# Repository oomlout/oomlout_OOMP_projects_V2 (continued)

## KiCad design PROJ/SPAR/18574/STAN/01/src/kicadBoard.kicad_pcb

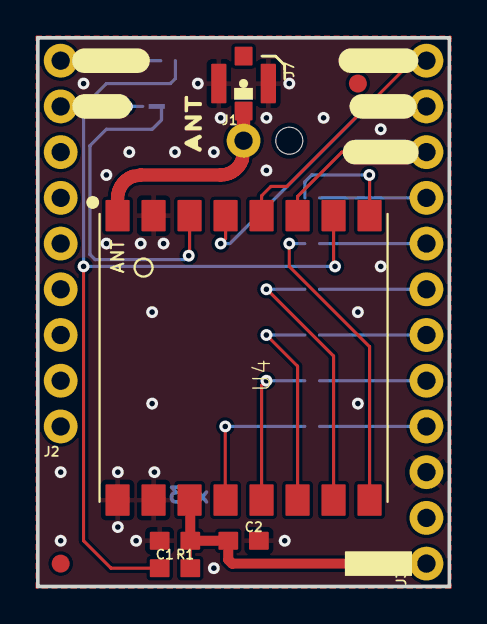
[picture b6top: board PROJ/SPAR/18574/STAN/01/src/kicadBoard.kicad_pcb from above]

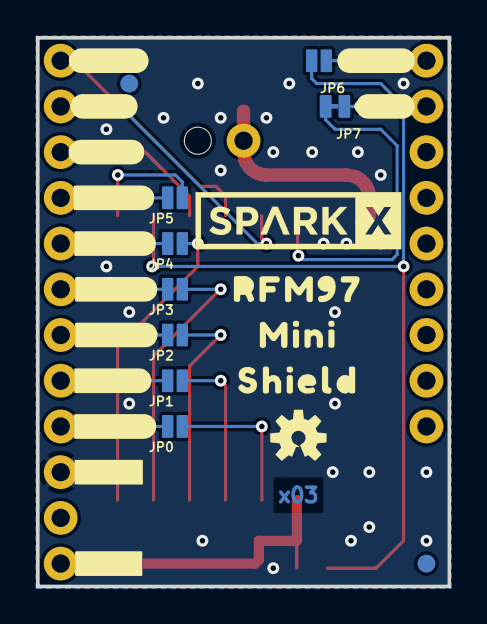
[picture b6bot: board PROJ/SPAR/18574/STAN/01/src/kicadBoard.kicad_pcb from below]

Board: 2 copper layers, 22.9 x 30.5 mm, 47 parts (28 on the bottom side), 22 nets.

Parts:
@HOLE0: (no value)
C1: 10uF; 0603
C2: 0.1uF; 0603
FID1, FID2, FID3, FID4: FIDUCIAL1X2; FIDUCIAL-1X2
FRAME1: FRAME-LETTER; CREATIVE_COMMONS
J1: 1X01_NO_SILK
J2: 1X09_NO_SILK
J3: 1X12_NO_SILK
J7: U.FL
JP0, JP1, JP2, JP3, JP4, JP5, JP6: JUMPER-SMT_2_NO_NO-SILK; SMT-JUMPER_2_NO_NO-SILK
JP7: JUMPER-SMT_2_NC_TRACE_NO-SILK; SMT-JUMPER_2_NC_TRACE_NO-SILK
LOGO2: OSHW-LOGOS; OSHW-LOGO-S
R1: 10k; 0603
U4: RFM97CW; RFM97
U$1: ANT0
U$2, U$21: ##CS##2
U$3, U$7: #SDO#0
U$4, U$6: #SDI#1
U$5, U$12: #SCK#0
U$8, U$9: #3V3#0
U$10: #GND#1
U$11: MINI0
U$13, U$17: ##RST##0
U$19: RFM970
U$20: SHIELD2
U$22: SPARKX-LOGO5; SPARKX-LARGE
U$23: #DIO0#0
U$24: #DIO1#0
U$25: #DIO2#0
U$26: #DIO3#0
U$27: #DIO4#0
U$28: #DIO5#0

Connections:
3.3V: C1.1, C2.1, J3.1, R1.2, U4.3V3
ANT: J1.1, J7.FEED, U4.ANT
DIO0: JP0.1, U4.DIO0
DIO1: JP1.1, U4.DIO1
DIO2: JP2.1, U4.DIO2
DIO3: JP3.1, U4.DIO3
DIO4: JP4.1, U4.DIO4
DIO5: JP5.1, U4.DIO5
GND: C1.2, C2.2, J3.3, J7.1, J7.2, U4.GND, U4.GND@1, U4.GND@2
unnamed: J3.6, JP2.2
unnamed: J2.9, JP6.2
unnamed: J2.8, JP7.2
unnamed: J3.5, JP1.2
unnamed: J3.4, JP0.2
unnamed: J3.7, JP3.2
unnamed: J3.8, JP4.2
unnamed: J3.9, JP5.2
SCK: J3.10, U4.SCK
SDI: J3.11, U4.SDI
SDO: J3.12, U4.SDO
~CS: JP7.1, U4.!CS!
~RST: JP6.1, R1.1, U4.!RST

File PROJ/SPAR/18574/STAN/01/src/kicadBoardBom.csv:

"Id";"Designator";"Package";"Quantity";"Designation";"Supplier and ref";
1;"U$1";"ANT0";1;"";;;
2;"U$5,U$12";"#SCK#0";2;"";;;
3;"C1";"0603";1;"10uF";;;
4;"U4";"RFM97";1;"RFM97CW";;;
5;"U$4,U$6";"#SDI#1";2;"";;;
6;"J3";"1X12_NO_SILK";1;"";;;
7;"@HOLE0";"";1;"";;;
8;"U$8,U$9";"#3V3#0";2;"";;;
9;"FID2,FID1,FID4,FID3";"FIDUCIAL-1X2";4;"FIDUCIAL1X2";;;
10;"C2";"0603";1;"0.1uF";;;
11;"U$3,U$7";"#SDO#0";2;"";;;
12;"R1";"0603";1;"10k";;;
13;"U$21,U$2";"##CS##2";2;"";;;
14;"J1";"1X01_NO_SILK";1;"";;;
15;"FRAME1";"CREATIVE_COMMONS";1;"FRAME-LETTER";;;
16;"U$13,U$17";"##RST##0";2;"";;;
17;"J7";"U.FL";1;"U.FL";;;
18;"J2";"1X09_NO_SILK";1;"";;;
19;"JP6,JP2,JP4,JP1,JP0,JP3,JP5";"SMT-JUMPER_2_NO_NO-SILK";7;"JUMPER-SMT_2_NO_NO-SILK";;;
20;"U$23";"#DIO0#0";1;"";;;
21;"U$28";"#DIO5#0";1;"";;;
22;"U$19";"RFM970";1;"";;;
23;"U$10";"#GND#1";1;"";;;
24;"U$11";"MINI0";1;"";;;
25;"JP7";"SMT-JUMPER_2_NC_TRACE_NO-SILK";1;"JUMPER-SMT_2_NC_TRACE_NO-SILK";;;
26;"U$22";"SPARKX-LARGE";1;"SPARKX-LOGO5";;;
27;"U$26";"#DIO3#0";1;"";;;
28;"LOGO2";"OSHW-LOGO-S";1;"OSHW-LOGOS";;;
29;"U$24";"#DIO1#0";1;"";;;
30;"U$25";"#DIO2#0";1;"";;;
31;"U$27";"#DIO4#0";1;"";;;
32;"U$20";"SHIELD2";1;"";;;

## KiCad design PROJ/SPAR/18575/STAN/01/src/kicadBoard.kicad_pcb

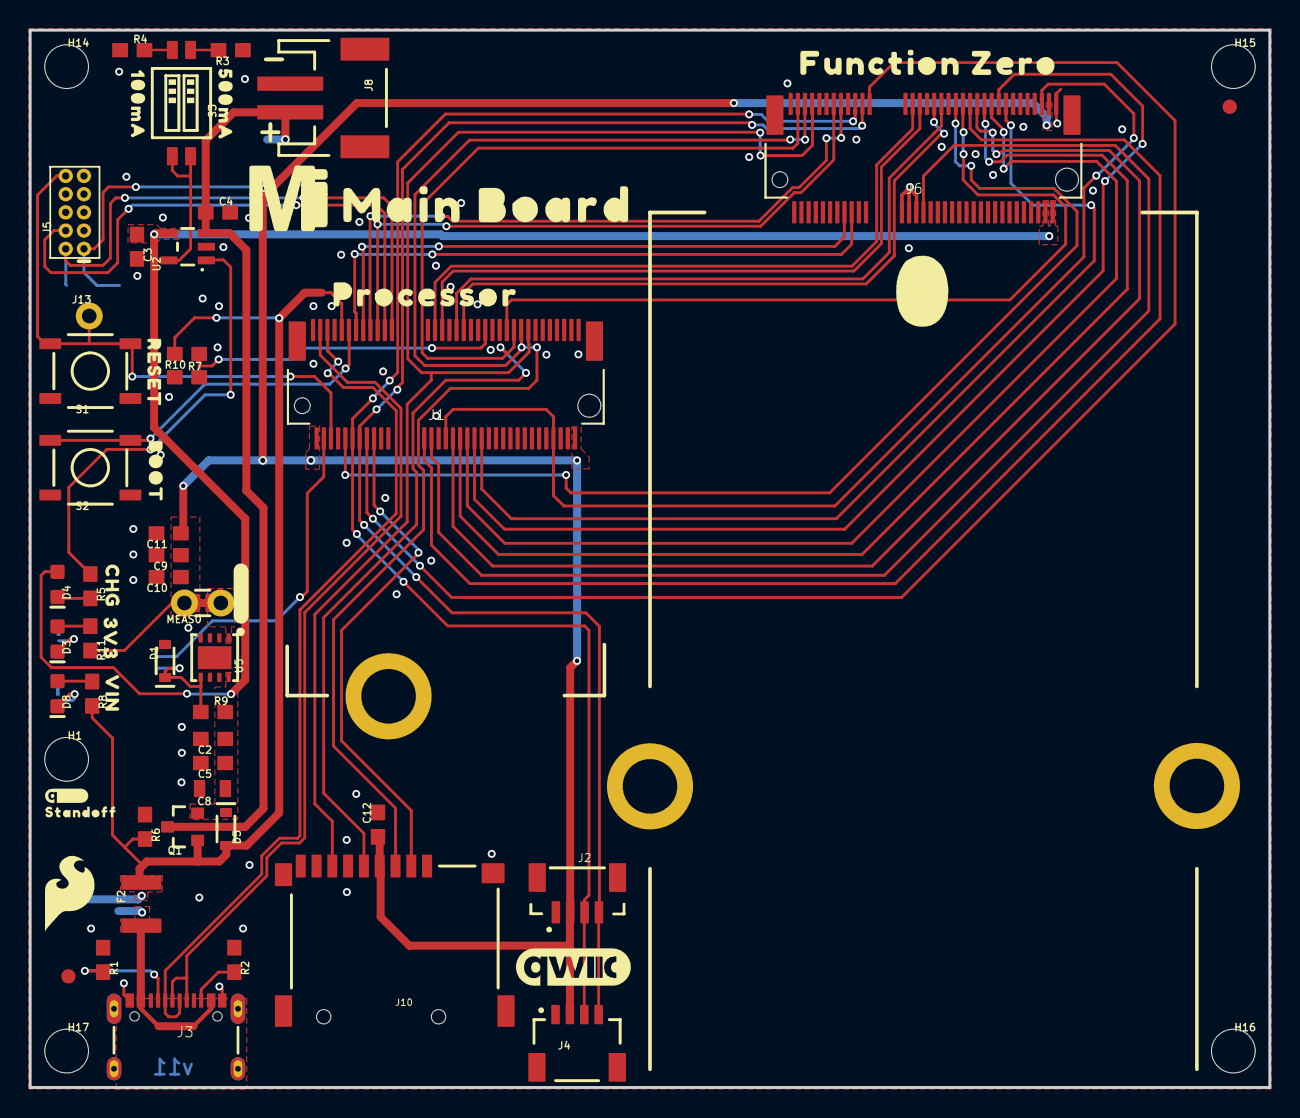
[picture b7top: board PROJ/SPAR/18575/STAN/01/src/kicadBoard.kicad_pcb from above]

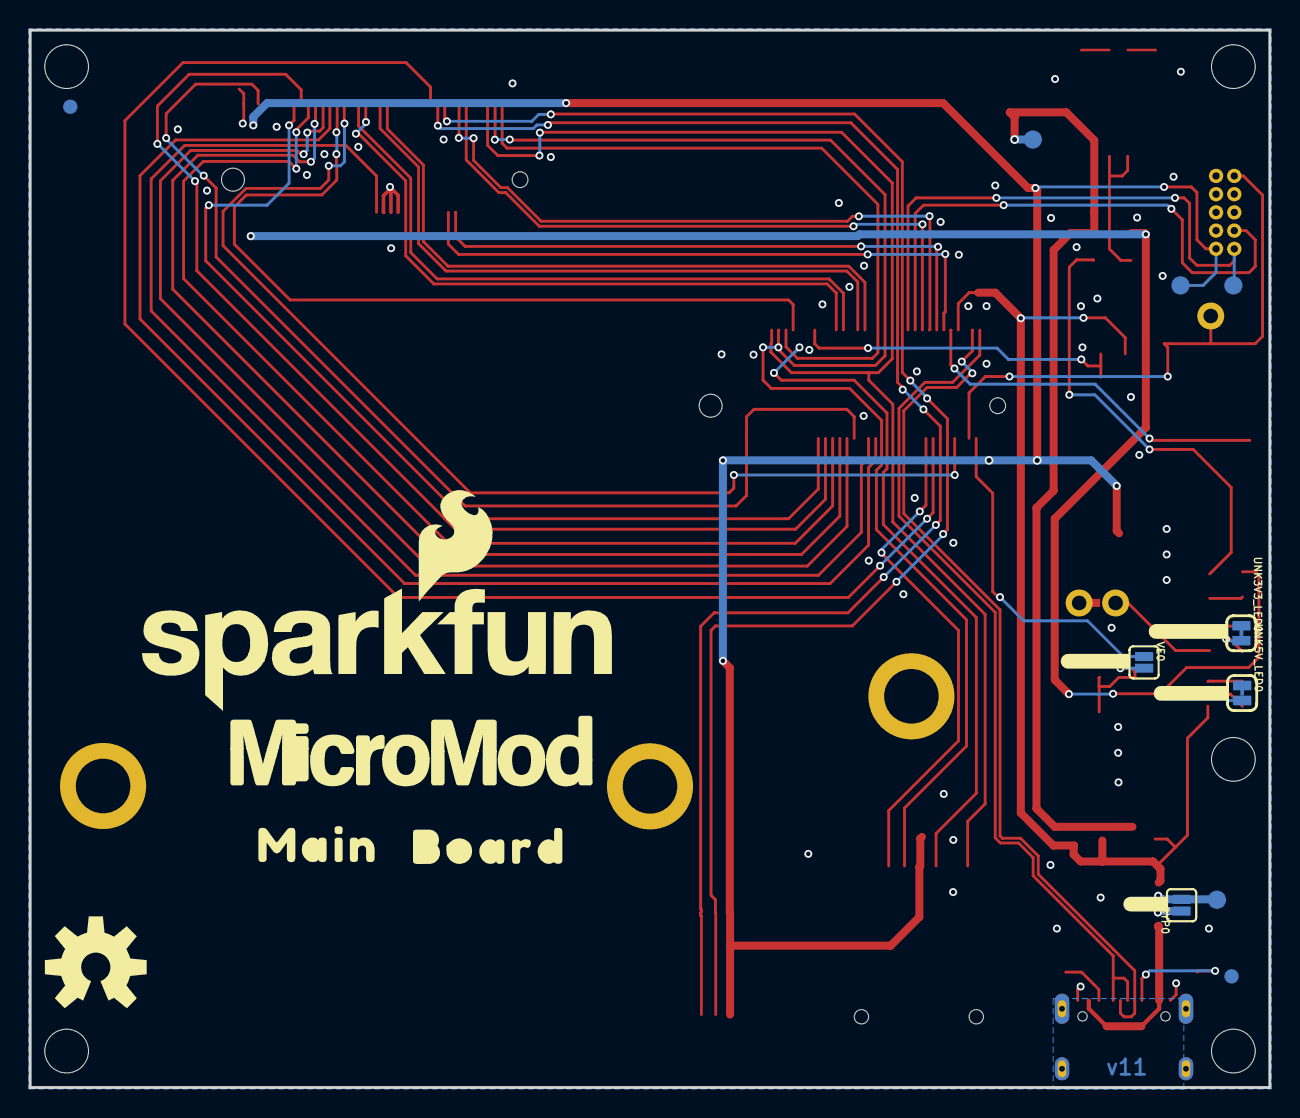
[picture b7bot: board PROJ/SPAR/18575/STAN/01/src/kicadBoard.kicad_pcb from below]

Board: 2 copper layers, 86.4 x 73.7 mm, 89 parts (19 on the bottom side), 52 nets.

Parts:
BYP0: JUMPER-SMT_2_NO_SILK; SMT-JUMPER_2_NO_SILK
C2, C11: 0.22uF; 0603
C3, C4: 4.7uF; 0603
C5, C10, C12: 0.1uF; 0603
C8: 10uF; 0805
C9: 1.0uF; 0603
D1: 3.3V; SOD-323
D3, D8: RED; LED-0603
D4: Yellow; LED-0603
D5: 1A/23V/620mV; SOD-323
F2: 6V/2A; 1210
FD1, FD2, FD3, FD4: FIDUCIAL1X2; FIDUCIAL-1X2
FRAME1: FRAME-LEDGER; CREATIVE_COMMONS
H1, H14, H15, H16, H17: STAND-OFFTIGHT; STAND-OFF-TIGHT
H3, H4, H8: STAND-OFF-REFLOW-M2.5_2.5MM_TALL; STAND-OFF-REFLOW-M2.5
J1: MICROMOD-2222-C; M.2-CONNECTOR-E
J2: Vertical Qwiic Connector; JST04_1MM_VERT
J3: USB-C-16P-2LAYER-PADS
J4: QWIIC_RIGHT_ANGLE; JST04_1MM_RA
J5: CORTEX_JTAG_DEBUG_MINIMUM_PTH; 2X5-PTH-1.27MM
J6: MICROMOD_FUNCTION_MAIN; M.2-CONNECTOR-E-FUNCTION-STANDARD
J8: JST-2-SMD
J10: MICRO-SD-PUSH-PUSH-EXT-PIN; MICROSD-EXTERNALPIN
J13: 1X01_NO_SILK
LOGO1: QWIIC_LOGO_8MM; QWIIC_8MM
LOGO2: SFE_LOGO_NAME_FLAME.3_INCH; SFE_LOGO_NAME_FLAME_.3
LOGO3: OSHW-LOGOL; OSHW-LOGO-L
MEAS0: JUMPER-COMBO_2_NC_TRACE; COMBO-JUMPER_2_NC_TRACE
Q1: 3.1A/30V/105mΩ; SOT23-3
R1, R2: 5.1k; 0603
R3: 2.0k; 0603
R4, R6, R7: 10k; 0603
R5, R11: 1k; 0603
R8: 4.7k; 0603
R9: 100k; 0603
R10: 20k; 0603
S1: Reset; TACTILE_SWITCH_SMD_5.2MM
S2: BOOT; TACTILE_SWITCH_SMD_5.2MM
S3: DIP-02-SMD-50MIL; DIPSWITCH-02-50MIL
TP1, TP2, TP3, TP4: TEST-POINT3X5; PAD.03X.05
U2: MCP73831; SOT23-5
U5: AP7361C-33; UDFN-8
U$1: 3V332530
U$2: VIN32529
U$3: CHG32528
U$4: FUNCTION_ZERO517
U$5: PROCESSOR522
U$6: #3V3_LED#17
U$7: #VIN_LED#16
U$8: #PTC#18
U$9: BOOT32541
U$10: RESET32540
U$11: #3V3_EN#18
U$12: MICROMOD_MI_LOGO_1
U$13: 0525
U$14: MICROMOD_LOGO_1
U$15: MAIN523
U$16: BOARD524
U$17: 100MA6
U$18: 500MA101
U$19: MAIN_BOARD5523
U$20: QWIIC_3MM
U$21: STANDOFF501
U$22: SFE_LOGO_FLAME_.2
U$23: #MEAS#40313513
UNK3V3_LED0, UNK5V_LED0: JUMPER-SMT_2_NC_TRACE_SILK; SMT-JUMPER_2_NC_TRACE_SILK
VE0: JUMPER-SMT_2_NO_SILK; SMT-JUMPER_2_NO_SILK

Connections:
3.3V: C9.1, C10.1, C11.1, C12.1, J1.2, J1.74, J2.2, J4.2, J5.1, J6.73, J10.4, MEAS0.2, MEAS0.4, R11.2, TP2.1
3.3V_EN: J1.4, VE0.1
3.3V_EN_VE: D3.A, R11.1
A0-PROCESSOR: J1.34, J6.38
CTS1-PROCESSOR: J1.15, J6.16
D0-PROCESSOR: J1.10, J6.47
D1-PROCESSOR/SD_CARD_~CS: J1.18, J10.2
D+: J1.3, J3.A6, J3.B6
D-: J1.5, J3.A7, J3.B7
G0-PROCESSOR: J1.40, J6.53
G1-PROCESSOR: J1.42, J6.55
G2-PROCESSOR: J1.44, J6.57
G3-PROCESSOR: J1.46, J6.59
G4-PROCESSOR: J1.48, J6.61
GND: C2.2, C3.2, C4.2, C5.2, C8.2, C9.2, C10.2, C11.2, C12.2, D1.A, H3.1, H4.1, H8.1, J1.1, J1.7, J1.33, J1.36, J1.39, J1.45, J1.75, J2.1, J3.GND, J3.GND2, J4.1, J5.3, J5.5, J5.9, J6.1, J6.32, J6.33, J6.34, J6.36, J6.39, J6.45, J6.75, J8.1, J10.6, J10.10, J10.11, J10.12, J10.13, R1.1, R2.1, R3.1, R4.1, R6.1, R7.1, S1.1, S1.2, S2.1, S2.2, U2.2, U5.4, U5.EP, UNK3V3_LED0.1, UNK5V_LED0.1
HOST_D+: J1.35, J6.35
HOST_D-: J1.37, J6.37
I2C_SCL: J1.14, J2.4, J4.4, J6.21
I2C_SDA: J1.12, J2.3, J4.3, J6.19
I2C_~INT: J1.16, J6.23
unnamed: D1.C, R9.1, U5.5, VE0.2
unnamed: BYP0.1, F2.1, J3.VBUS1, J3.VBUS2
unnamed: J3.A5, R1.2
unnamed: MEAS0.1, MEAS0.3, U5.1
unnamed: D8.A, R8.1
unnamed: R4.2, S3.2
unnamed: D4.C, R5.2
unnamed: D3.C, UNK3V3_LED0.2
unnamed: S3.3, S3.4, U2.5
unnamed: D8.C, UNK5V_LED0.2
unnamed: R5.1, U2.1
unnamed: R3.2, S3.1
PROCESSOR_CAN-RX: J1.41, J6.43
PROCESSOR_CAN-TX: J1.43, J6.41
PWM0-PROCESSOR: J1.32, J6.51
PWR_EN0: J1.38, J1.68, J6.71
RTS1-PROCESSOR: J1.13, J6.18
RX1-PROCESSOR: J1.19, J6.13
SHLD: J3.B5, R2.2
SPI_PROCESSOR_SCK: J1.57, J6.3, J10.5
SPI_PROCESSOR_SDI: J1.61, J6.7, J10.7
SPI_PROCESSOR_SDO: J1.59, J6.5, J10.3
SWDCK: J1.21, J5.4
SWDIO: J1.23, J5.2, TP1.1
TX1-PROCESSOR: J1.17, J6.15
VCC: C2.1, C3.1, C5.1, C8.1, D4.A, D5.C, J6.72, J6.74, Q1.2, R9.2, U2.4, U5.8
VIN: BYP0.2, D5.A, F2.2, J1.9, Q1.1, R6.2, R8.2, R10.2, TP4.1
VIN/3: J1.49, R7.2, R10.1
V_BATT: C4.1, J8.2, Q1.3, TP3.1, U2.3
~BOOT: J1.11, S2.3, S2.4
~CS0-PROCESSOR: J1.55, J6.49
~RESET: J1.6, J5.10, J13.1, S1.3, S1.4

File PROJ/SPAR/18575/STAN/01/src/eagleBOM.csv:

"Part";"Value";"Device";"Package";"Description";"DESIGNER";"PROD_ID";"REV";"SF_ID";"VALUE";
"3V3_LED";"JUMPER-SMT_2_NC_TRACE_SILK";"JUMPER-SMT_2_NC_TRACE_SILK";"SMT-JUMPER_2_NC_TRACE_SILK";"Normally closed trace jumper";"";"";"";"";"";
"5V_LED";"JUMPER-SMT_2_NC_TRACE_SILK";"JUMPER-SMT_2_NC_TRACE_SILK";"SMT-JUMPER_2_NC_TRACE_SILK";"Normally closed trace jumper";"";"";"";"";"";
"BYP";"JUMPER-SMT_2_NO_SILK";"JUMPER-SMT_2_NO_SILK";"SMT-JUMPER_2_NO_SILK";"Normally open jumper";"";"";"";"";"";
"C2";"0.22uF";"0.22UF-0603-25V-10%";"0603";"0.22µF ceramic capacitors";"";"CAP-07822";"";"";"0.22uF";
"C3";"4.7uF";"4.7UF-0603-6.3V-(10%)";"0603";"4.7µF ceramic capacitors";"";"CAP-08280";"";"";"4.7uF";
"C4";"4.7uF";"4.7UF-0603-35V-(20%)";"0603";"4.7µF ceramic capacitors";"";"CAP-14106";"";"";"4.7uF";
"C5";"0.1uF";"0.1UF-0603-25V-(+80/-20%)";"0603";"0.1µF ceramic capacitors";"";"CAP-00810";"";"";"0.1uF";
"C8";"10uF";"10UF-0805-10V-10%";"0805";"10.0µF ceramic capacitors";"";"CAP-11330";"";"";"10uF";
"C9";"1.0uF";"1.0UF-0603-16V-10%";"0603";"1µF ceramic capacitors";"";"CAP-00868";"";"";"1.0uF";
"C10";"0.1uF";"0.1UF-0603-25V-(+80/-20%)";"0603";"0.1µF ceramic capacitors";"";"CAP-00810";"";"";"0.1uF";
"C11";"0.22uF";"0.22UF-0603-25V-10%";"0603";"0.22µF ceramic capacitors";"";"CAP-07822";"";"";"0.22uF";
"C12";"0.1uF";"0.1UF-0603-25V-(+80/-20%)";"0603";"0.1µF ceramic capacitors";"";"CAP-00810";"";"";"0.1uF";
"D1";"3.3V";"DIODE-ZENER-MM3Z3V3T1G";"SOD-323";"Zener Diode";"";"DIO-11284";"";"";"3.3V";
"D3";"RED";"LED-RED0603";"LED-0603";"Red SMD LED";"";"DIO-00819";"";"";"RED";
"D4";"Yellow";"LED-YELLOW0603";"LED-0603";"Yellow SMD LED";"";"DIO-09003";"";"";"Yellow";
"D5";"1A/23V/620mV";"DIODE-SCHOTTKY-BAT20J";"SOD-323";"Schottky diode";"";"DIO-11623";"";"";"1A/23V/620mV";
"D8";"RED";"LED-RED0603";"LED-0603";"Red SMD LED";"";"DIO-00819";"";"";"RED";
"F2";"6V/2A";"PPTC_6V2A";"1210";"Resettable Fuse PPTC";"";"RES-14313";"";"";"6V/2A";
"FD1";"FIDUCIAL1X2";"FIDUCIAL1X2";"FIDUCIAL-1X2";"Fiducial Alignment Points";"";"";"";"";"";
"FD2";"FIDUCIAL1X2";"FIDUCIAL1X2";"FIDUCIAL-1X2";"Fiducial Alignment Points";"";"";"";"";"";
"FD3";"FIDUCIAL1X2";"FIDUCIAL1X2";"FIDUCIAL-1X2";"Fiducial Alignment Points";"";"";"";"";"";
"FD4";"FIDUCIAL1X2";"FIDUCIAL1X2";"FIDUCIAL-1X2";"Fiducial Alignment Points";"";"";"";"";"";
"FRAME1";"FRAME-LEDGER";"FRAME-LEDGER";"CREATIVE_COMMONS";"Schematic Frame - Ledger";"";"";"";"";"";
"H3";"STAND-OFF-REFLOW-M2.5_2.5MM_TALL";"STAND-OFF-REFLOW-M2.5_2.5MM_TALL";"STAND-OFF-REFLOW-M2.5";"Stand Off Reflow Compatible";"";"HW-14899";"";"";"";
"H4";"STAND-OFF-REFLOW-M2.5_2.5MM_TALL";"STAND-OFF-REFLOW-M2.5_2.5MM_TALL";"STAND-OFF-REFLOW-M2.5";"Stand Off Reflow Compatible";"";"HW-14899";"";"";"";
"H8";"STAND-OFF-REFLOW-M2.5_2.5MM_TALL";"STAND-OFF-REFLOW-M2.5_2.5MM_TALL";"STAND-OFF-REFLOW-M2.5";"Stand Off Reflow Compatible";"";"HW-14899";"";"";"";
"H14";"STAND-OFFTIGHT";"STAND-OFFTIGHT";"STAND-OFF-TIGHT";"Stand Off";"";"";"";"";"";
"H15";"STAND-OFFTIGHT";"STAND-OFFTIGHT";"STAND-OFF-TIGHT";"Stand Off";"";"";"";"";"";
"H16";"STAND-OFFTIGHT";"STAND-OFFTIGHT";"STAND-OFF-TIGHT";"Stand Off";"";"";"";"";"";
"H17";"STAND-OFFTIGHT";"STAND-OFFTIGHT";"STAND-OFF-TIGHT";"Stand Off";"";"";"";"";"";
"J1";"MICROMOD-2222-C";"MICROMOD-2222-C";"M.2-CONNECTOR-E";"MicroMod Connector";"";"CONN-14877";"";"";"";
"J2";"Vertical Qwiic Connector";"QWIIC_CONNECTOR";"JST04_1MM_VERT";"SparkFun I2C Standard Qwiic Connector";"";"CONN-14483";"";"";"Vertical Qwiic Connector";
"J3";"";"USB_C_2-LAYER_PADS";"USB-C-16P-2LAYER-PADS";"USB Type C 16Pin Connector";"";"CONN-14122";"";"";"";
"J4";"QWIIC_RIGHT_ANGLE";"QWIIC_CONNECTORJS-1MM";"JST04_1MM_RA";"SparkFun I2C Standard Qwiic Connector";"";"CONN-13694";"";"";"QWIIC_RIGHT_ANGLE";
"J5";"CORTEX_JTAG_DEBUG_MINIMUM_PTH";"CORTEX_JTAG_DEBUG_MINIMUM_PTH";"2X5-PTH-1.27MM";"Cortex Debug Connector - 10 pin";"";"";"";"";"";
"J6";"MICROMOD_FUNCTION_MAIN";"MICROMOD_FUNCTION_MAIN";"M.2-CONNECTOR-E-FUNCTION-STANDARD";"MicroMod Connector";"";"CONN-14877";"";"";"";
"J8";"";"JST_2MM_MALE";"JST-2-SMD";"JST 2MM MALE RA CONNECTOR";"";"CONN-11443";"";"PRT-08612";"";
"J10";"MICRO-SD-PUSH-PUSH-EXT-PIN";"MICRO-SD-PUSH-PUSH-EXT-PIN";"MICROSD-EXTERNALPIN";"microSD Socket for Transflash";"";"CONN-16110";"";"";"";
"J13";"";"CONN_01PTH_NO_SILK_YES_STOP";"1X01_NO_SILK";"Single connection point. Often used as Generic Header-pin footprint for 0.1 inch spaced/style header connections";"";"";"";"";"";
"LOGO1";"QWIIC_LOGO_8MM";"QWIIC_LOGO_8MM";"QWIIC_8MM";"Qwiic Logos for placement on schematic and PCB. The 5.5mm silk logo is best for placing next to Qwiic connector.";"";"";"";"";"";
"LOGO2";"SFE_LOGO_NAME_FLAME.3_INCH";"SFE_LOGO_NAME_FLAME.3_INCH";"SFE_LOGO_NAME_FLAME_.3";"SparkFun Font Logo w/ Flame";"";"";"";"";"";
"LOGO3";"OSHW-LOGOL";"OSHW-LOGOL";"OSHW-LOGO-L";"Open-Source Hardware (OSHW) Logo";"";"";"";"";"";
"MEAS";"JUMPER-COMBO_2_NC_TRACE";"JUMPER-COMBO_2_NC_TRACE";"COMBO-JUMPER_2_NC_TRACE";"";"";"";"";"";"";
"Q1";"3.1A/30V/105mΩ";"MOSFET_PCH-DMG2307L";"SOT23-3";"P-channel MOSFETs";"";"TRANS-11308";"";"";"3.1A/30V/105mΩ";
"R1";"5.1k";"5.1KOHM5.1KOHM-0603-1/10W-1%";"0603";"";"";"RES-12083";"";"";"5.1k";
"R2";"5.1k";"5.1KOHM5.1KOHM-0603-1/10W-1%";"0603";"";"";"RES-12083";"";"";"5.1k";
"R3";"2.0k";"2.0KOHM-0603-1/10W-5%";"0603";"2kΩ resistor";"";"RES-08296";"";"";"2.0k";
"R4";"10k";"10KOHM-0603-1/10W-1%";"0603";"10kΩ resistor";"";"RES-00824";"";"";"10k";
"R5";"1k";"1KOHM-0603-1/10W-1%";"0603";"1kΩ resistor";"";"RES-07856";"";"";"1k";
"R6";"10k";"10KOHM-0603-1/10W-1%";"0603";"10kΩ resistor";"";"RES-00824";"";"";"10k";
"R7";"10k";"10KOHM-0603-1/10W-1%";"0603";"10kΩ resistor";"";"RES-00824";"";"";"10k";
"R8";"4.7k";"4.7KOHM-0603-1/10W-1%";"0603";"4.7kΩ resistor";"";"RES-07857";"";"";"4.7k";
"R9";"100k";"100KOHM-0603-1/10W-1%";"0603";"100kΩ resistor";"";"RES-07828";"";"";"100k";
"R10";"20k";"20KOHM-0603-1/10W-1%";"0603";"20kΩ resistor";"";"RES-09383";"";"";"20k";
"R11";"1k";"1KOHM-0603-1/10W-1%";"0603";"1kΩ resistor";"";"RES-07856";"";"";"1k";
"S1";"Reset";"MOMENTARY-SWITCH-SPST-SMD-5.2-TALL-REDUNDANT";"TACTILE_SWITCH_SMD_5.2MM";"Momentary Switch (Pushbutton) - SPST";"";"SWCH-14139";"";"";"";
"S2";"BOOT";"MOMENTARY-SWITCH-SPST-SMD-5.2-TALL-REDUNDANT";"TACTILE_SWITCH_SMD_5.2MM";"Momentary Switch (Pushbutton) - SPST";"";"SWCH-14139";"";"";"";
"S3";"DIP-02-SMD-50MIL";"DIP-02-SMD-50MIL";"DIPSWITCH-02-50MIL";"2-Position DIP Switch";"";"SWCH-13215";"";"";"";
"TP1";"TEST-POINT3X5";"TEST-POINT3X5";"PAD.03X.05";"SparkFun Test Points";"";"";"";"";"";
"TP2";"TEST-POINT3X5";"TEST-POINT3X5";"PAD.03X.05";"SparkFun Test Points";"";"";"";"";"";
"TP3";"TEST-POINT3X5";"TEST-POINT3X5";"PAD.03X.05";"SparkFun Test Points";"";"";"";"";"";
"TP4";"TEST-POINT3X5";"TEST-POINT3X5";"PAD.03X.05";"SparkFun Test Points";"";"";"";"";"";
"U2";"MCP73831";"MCP73831";"SOT23-5";"MCP73831T Li-Ion, Li-Pol Controller";"";"IC-09995";"";"";"";
"U5";"AP7361C-33";"AP7361C-33FGEUDFN-8";"UDFN-8";"AP7361C 3.3V LDO Regulator";"";"VREG-14094";"";"";"";
"VE";"JUMPER-SMT_2_NO_SILK";"JUMPER-SMT_2_NO_SILK";"SMT-JUMPER_2_NO_SILK";"Normally open jumper";"";"";"";"";"";
